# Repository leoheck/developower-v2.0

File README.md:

## Developower-v2.0

This project is an effort to recreate Developower-v2.0 board on Kicad.

This is the Developower-v2.0 board used on those Chinese 3018 CNC's.

This is the current version of the layout, but it is still a work in progress.

A simple cover for the board can be found here too.

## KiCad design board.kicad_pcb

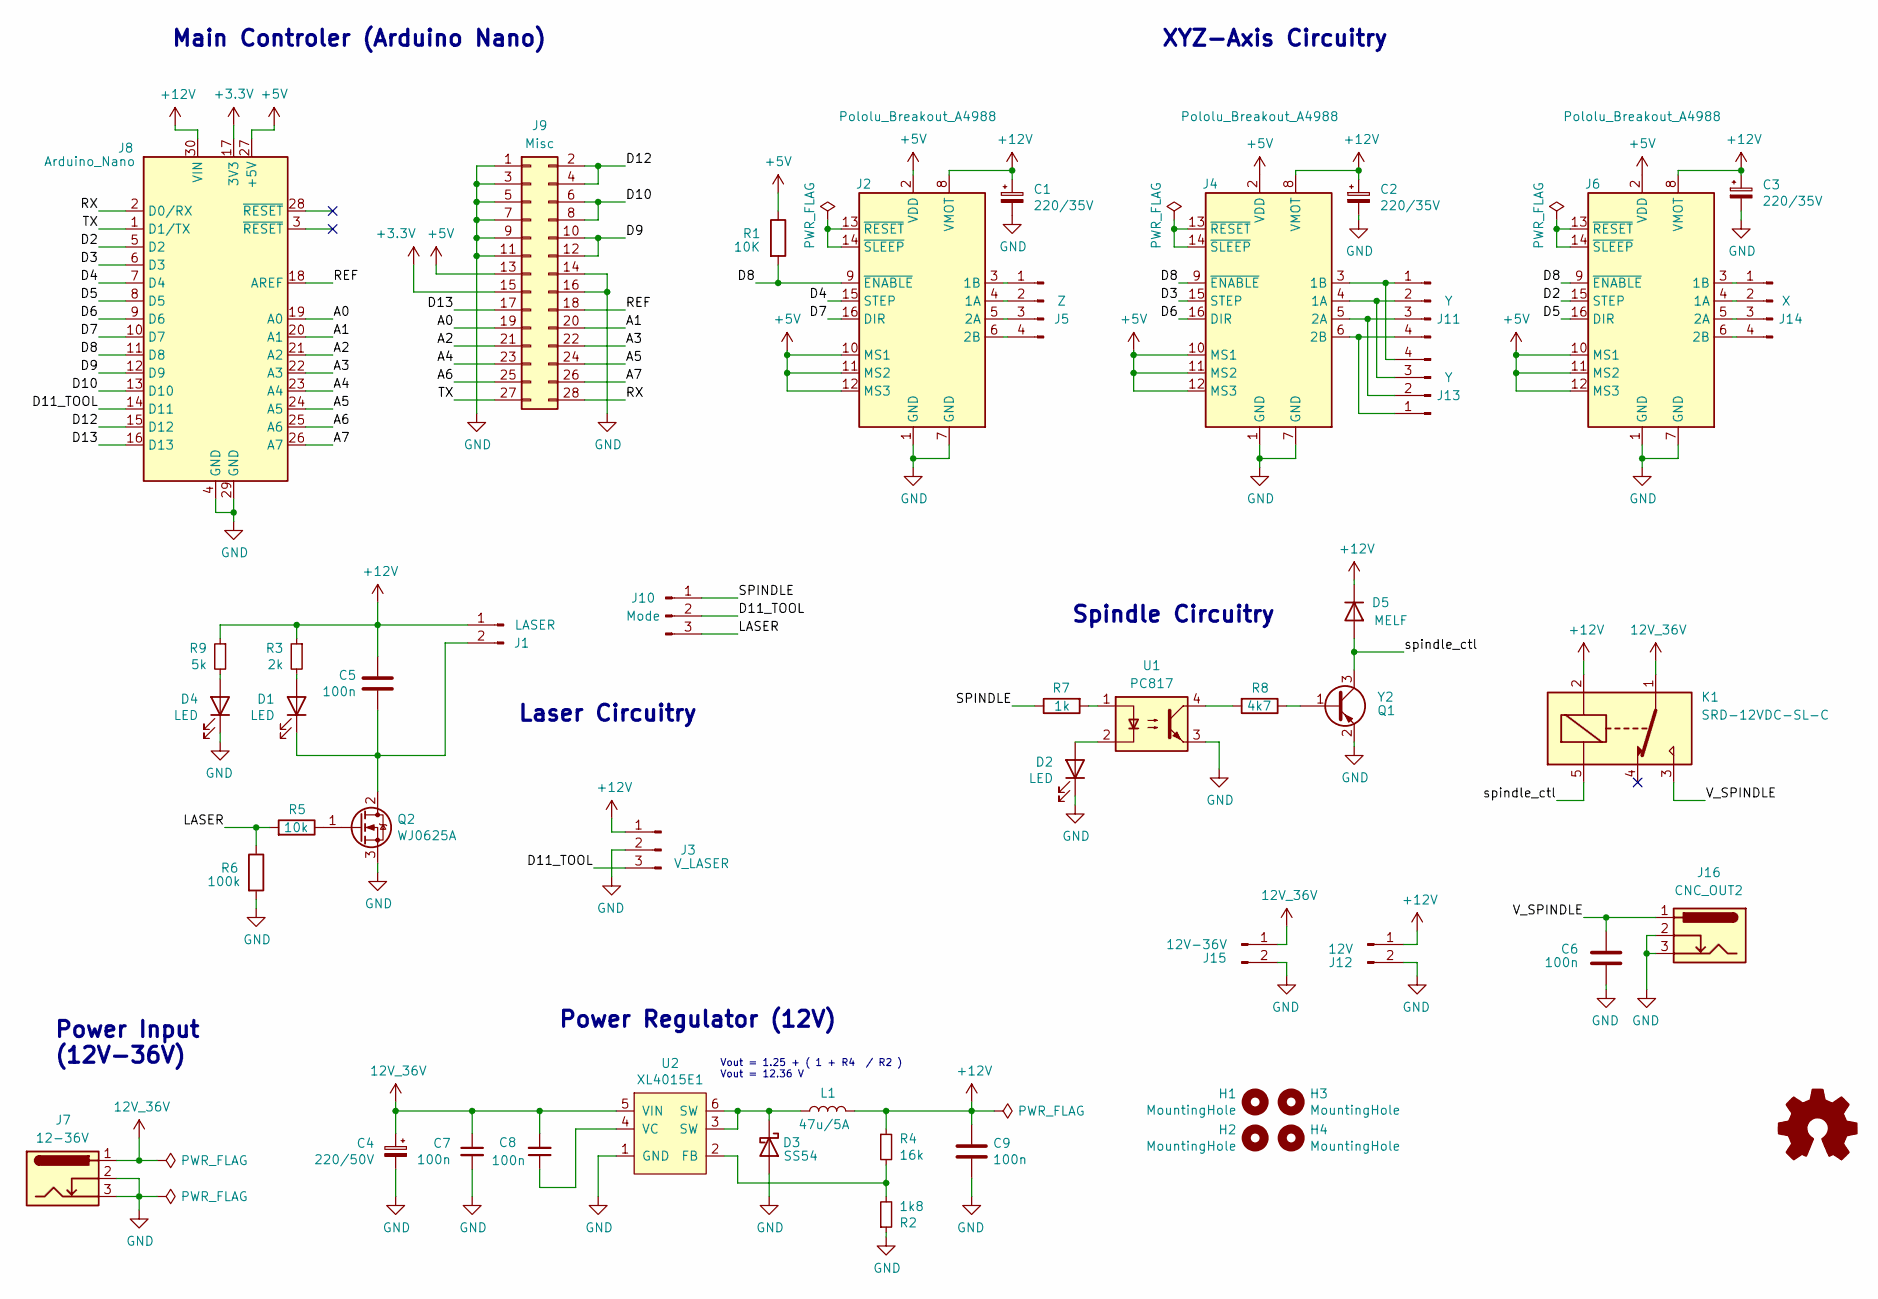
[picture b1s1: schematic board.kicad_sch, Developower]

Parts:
C1, C2, C3: 220/35V; CP_Elec_8x10
C4: 220/50V; CP_Elec_10x10.5
C5, C6: 100n; C_1206_3216Metric
C7, C8, C9: 100n; C_0805_2012Metric
D1, D2, D4: LED; LED_0603_1608Metric
D3: SS54; D_2512_6332Metric
D5: MELF; D_MiniMELF
H1, H2, H3, H4: MountingHole; MountingHole_3.2mm_M3
J1: LASER; JST_S2B-XH-A(LF)(SN)
J2, J4, J6: Pololu_Breakout_A4988; Pololu_Breakout-16_15.2x20.3mm
J3: V_LASER; JST_S3B-XH-A(LF)(SN)
J5: Z; JST_S4B-XH-A(LF)(SN)
J7: 12-36V; BarrelJack_Horizontal
J8: Arduino_Nano
J9: Misc; PinHeader_2x14_P2.54mm_Vertical
J10: Mode; PinHeader_1x03_P2.54mm_Vertical
J11, J13: Y; JST_S4B-XH-A(LF)(SN)
J12: 12V; JST_S2B-XH-A(LF)(SN)
J14: X; JST_S4B-XH-A(LF)(SN)
J15: 12V-36V; JST_S2B-XH-A(LF)(SN)
J16: CNC_OUT2; BarrelJack_Horizontal
K1: SRD-12VDC-SL-C; Relay_SPDT_SANYOU_SRD_Series_Form_C
L1: 47u/5A; L_Vishay_IHLP-4040
Q1: Y2; SC-59
Q2: WJ0625A; TO-252-2
R1: 10K; R_0805_2012Metric
R2: 1k8; R_0805_2012Metric
R3: 2k; R_0805_2012Metric
R4: 16k; R_0805_2012Metric
R5: 10k; R_0805_2012Metric
R6: 100k; R_0805_2012Metric
R7: 1k; R_0805_2012Metric
R8: 4k7; R_0805_2012Metric
R9: 5k; R_0805_2012Metric
T1: Logo_Open_Hardware_Small; chinese-text
U1: PC817; SMDIP-4_W9.53mm
U2: XL4015E1; TO-263-5_TabPin6

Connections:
12V_36V: C4.1, C7.1, C8.2, J7.1, J15.1, K1.1, U2.5 (VIN)
+3V3: J8.17 (3V3), J9.15
+5V: J2.2 (VDD), J2.10 (MS1), J2.11 (MS2), J2.12 (MS3), J4.2 (VDD), J4.10 (MS1), J4.11 (MS2), J4.12 (MS3), J6.2 (VDD), J6.10 (MS1), J6.11 (MS2), J6.12 (MS3), J8.27 (+5V), J9.13, R1.1
+12V: C1.1, C2.1, C3.1, C5.1, C9.1, D5.1 (K), J1.1, J2.8 (VMOT), J3.1, J4.8 (VMOT), J6.8 (VMOT), J8.30 (VIN), J12.1, K1.2, L1.2, R3.1, R4.1, R9.1
/A0: J8.19 (A0), J9.19
/A1: J8.20 (A1), J9.20
/A2: J8.21 (A2), J9.21
/A3: J8.22 (A3), J9.22
/A4: J8.23 (A4), J9.23
/A5: J8.24 (A5), J9.24
/A6: J8.25 (A6), J9.25
/A7: J8.26 (A7), J9.26
/D2: J6.15 (STEP), J8.5 (D2)
/D3: J4.15 (STEP), J8.6 (D3)
/D4: J2.15 (STEP), J8.7 (D4)
/D5: J6.16 (DIR), J8.8 (D5)
/D6: J4.16 (DIR), J8.9 (D6)
/D7: J2.16 (DIR), J8.10 (D7)
/D8: J2.9 (~ENABLE), J4.9 (~ENABLE), J6.9 (~ENABLE), J8.11 (D8), R1.2
/D9: J8.12 (D9), J9.10, J9.12
/D10: J8.13 (D10), J9.6, J9.8
/D11_TOOL: J3.3, J8.14 (D11), J10.2
/D12: J8.15 (D12), J9.2, J9.4
/D13: J8.16 (D13), J9.17
/LASER: J10.3, R5.2, R6.1
/REF: J8.18 (AREF), J9.18
/RX: J8.2 (D0/RX), J9.28
/SPINDLE: J10.1, R7.1
/TX: J8.1 (D1/TX), J9.27
/V_SPINDLE: C6.2, J16.1, K1.3
/spindle_ctl: D5.2 (A), K1.5, Q1.3 (C)
GND: C1.2, C2.2, C3.2, C4.2, C6.1, C7.2, C9.2, D2.1 (K), D3.2 (A), D4.1 (K), J2.1 (GND), J2.7 (GND), J3.2, J4.1 (GND), J4.7 (GND), J6.1 (GND), J6.7 (GND), J7.2, J7.3, J8.4 (GND), J8.29 (GND), J9.1, J9.3, J9.5, J9.7, J9.9, J9.11, J9.14, J9.16, J12.2, J15.2, J16.2, J16.3, Q1.2 (E), Q2.3 (S), R2.1, R6.2, U1.3, U2.1 (GND)
unnamed: C5.2, D1.1 (K), J1.2, Q2.2 (D)
unnamed: C8.1, U2.4 (VC)
unnamed: D1.2 (A), R3.2
unnamed: D2.2 (A), U1.2
unnamed: D3.1 (K), L1.1, U2.3 (SW), U2.6 (SW)
unnamed: D4.2 (A), R9.2
unnamed: J2.3 (1B), J5.1
unnamed: J2.4 (1A), J5.2
unnamed: J2.5 (2A), J5.3
unnamed: J2.6 (2B), J5.4
unnamed: J2.13 (~RESET), J2.14 (~SLEEP)
unnamed: J4.13 (~RESET), J4.14 (~SLEEP)
unnamed: J6.13 (~RESET), J6.14 (~SLEEP)
unnamed: J4.3 (1B), J11.1, J13.4
unnamed: J4.4 (1A), J11.2, J13.3
unnamed: J4.5 (2A), J11.3, J13.2
unnamed: J4.6 (2B), J11.4, J13.1
unnamed: J6.3 (1B), J14.1
unnamed: J6.4 (1A), J14.2
unnamed: J6.5 (2A), J14.3
unnamed: J6.6 (2B), J14.4
unnamed: Q1.1 (B), R8.1
unnamed: Q2.1 (G), R5.1
unnamed: R2.2, R4.2, U2.2 (FB)
unnamed: R7.2, U1.1
unnamed: R8.2, U1.4

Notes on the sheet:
Laser Circuitry
XYZ-Axis Circuitry
Vout = 1.25 + ( 1 + R4 / R2 ) Vout = 12.36 V
Power Regulator (12V)
Power Input (12V-36V)
Spindle Circuitry
Main Controler (Arduino Nano)

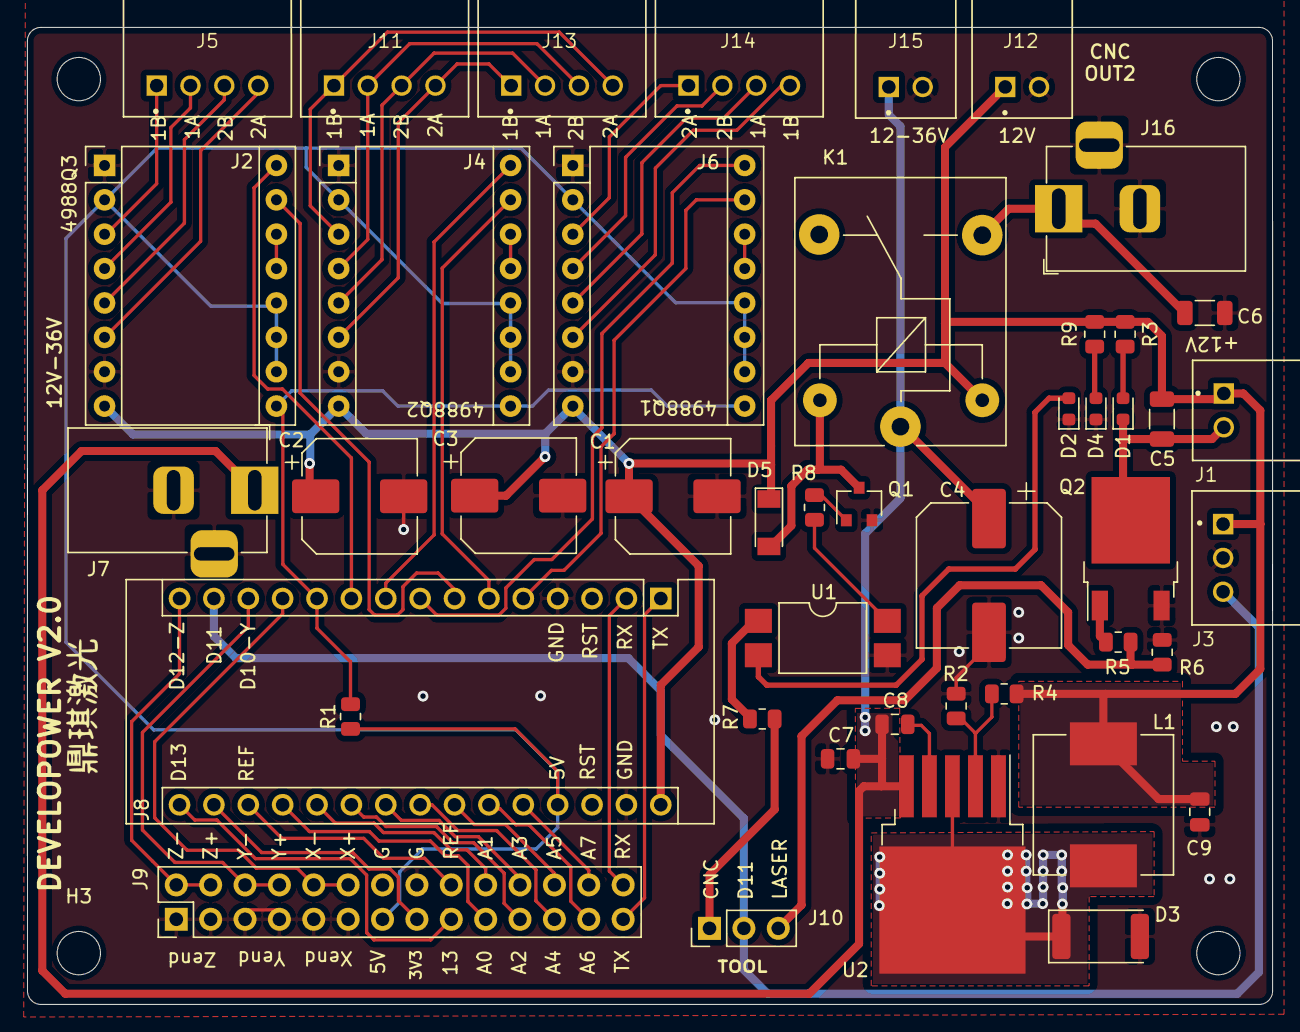
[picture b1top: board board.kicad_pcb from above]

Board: 2 copper layers, 92.0 x 72.2 mm, 50 parts (0 on the bottom side), 58 nets.

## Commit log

2019-12-23 Initialize project
2019-12-23 Add board image
2021-04-20 Add more details (extra components, footprints and 3d models)
2021-04-20 Fix images
2021-04-20 Add white background
2021-04-21 Add some interconnections. Fix some missing 3d models.
2021-04-21 Connect extra signals, 90% done
2021-04-22 Add extra power symbol
2021-04-22 Improve connections
2021-04-22 Add 3d printed cover
2021-04-22 Add JST XH headers and improve other parts
2021-04-23 Fix description of the power source
2021-04-23 Update some parts
2021-04-23 Fix case
2021-04-24 Add missing connection to the GND
2021-04-24 Fix n-mosfet symbol/footprint and improve circuit
2021-04-24 Update image
2021-04-24 Update Q1
2021-04-24 Crop margins
2021-04-24 Organize schematic sheet
2021-04-24 Update board image
2021-04-24 Reduce ERC
2021-04-24 Reduce DRC
2021-04-26 Improve parts placement
2021-04-26 Organize housing-related files
2021-04-26 Update case
2021-04-26 Power on the Arduino
2021-12-30 Organize schematic a bit
2021-12-30 Convert project to Kicad v6
2023-04-01 Convert to Kicad 7
